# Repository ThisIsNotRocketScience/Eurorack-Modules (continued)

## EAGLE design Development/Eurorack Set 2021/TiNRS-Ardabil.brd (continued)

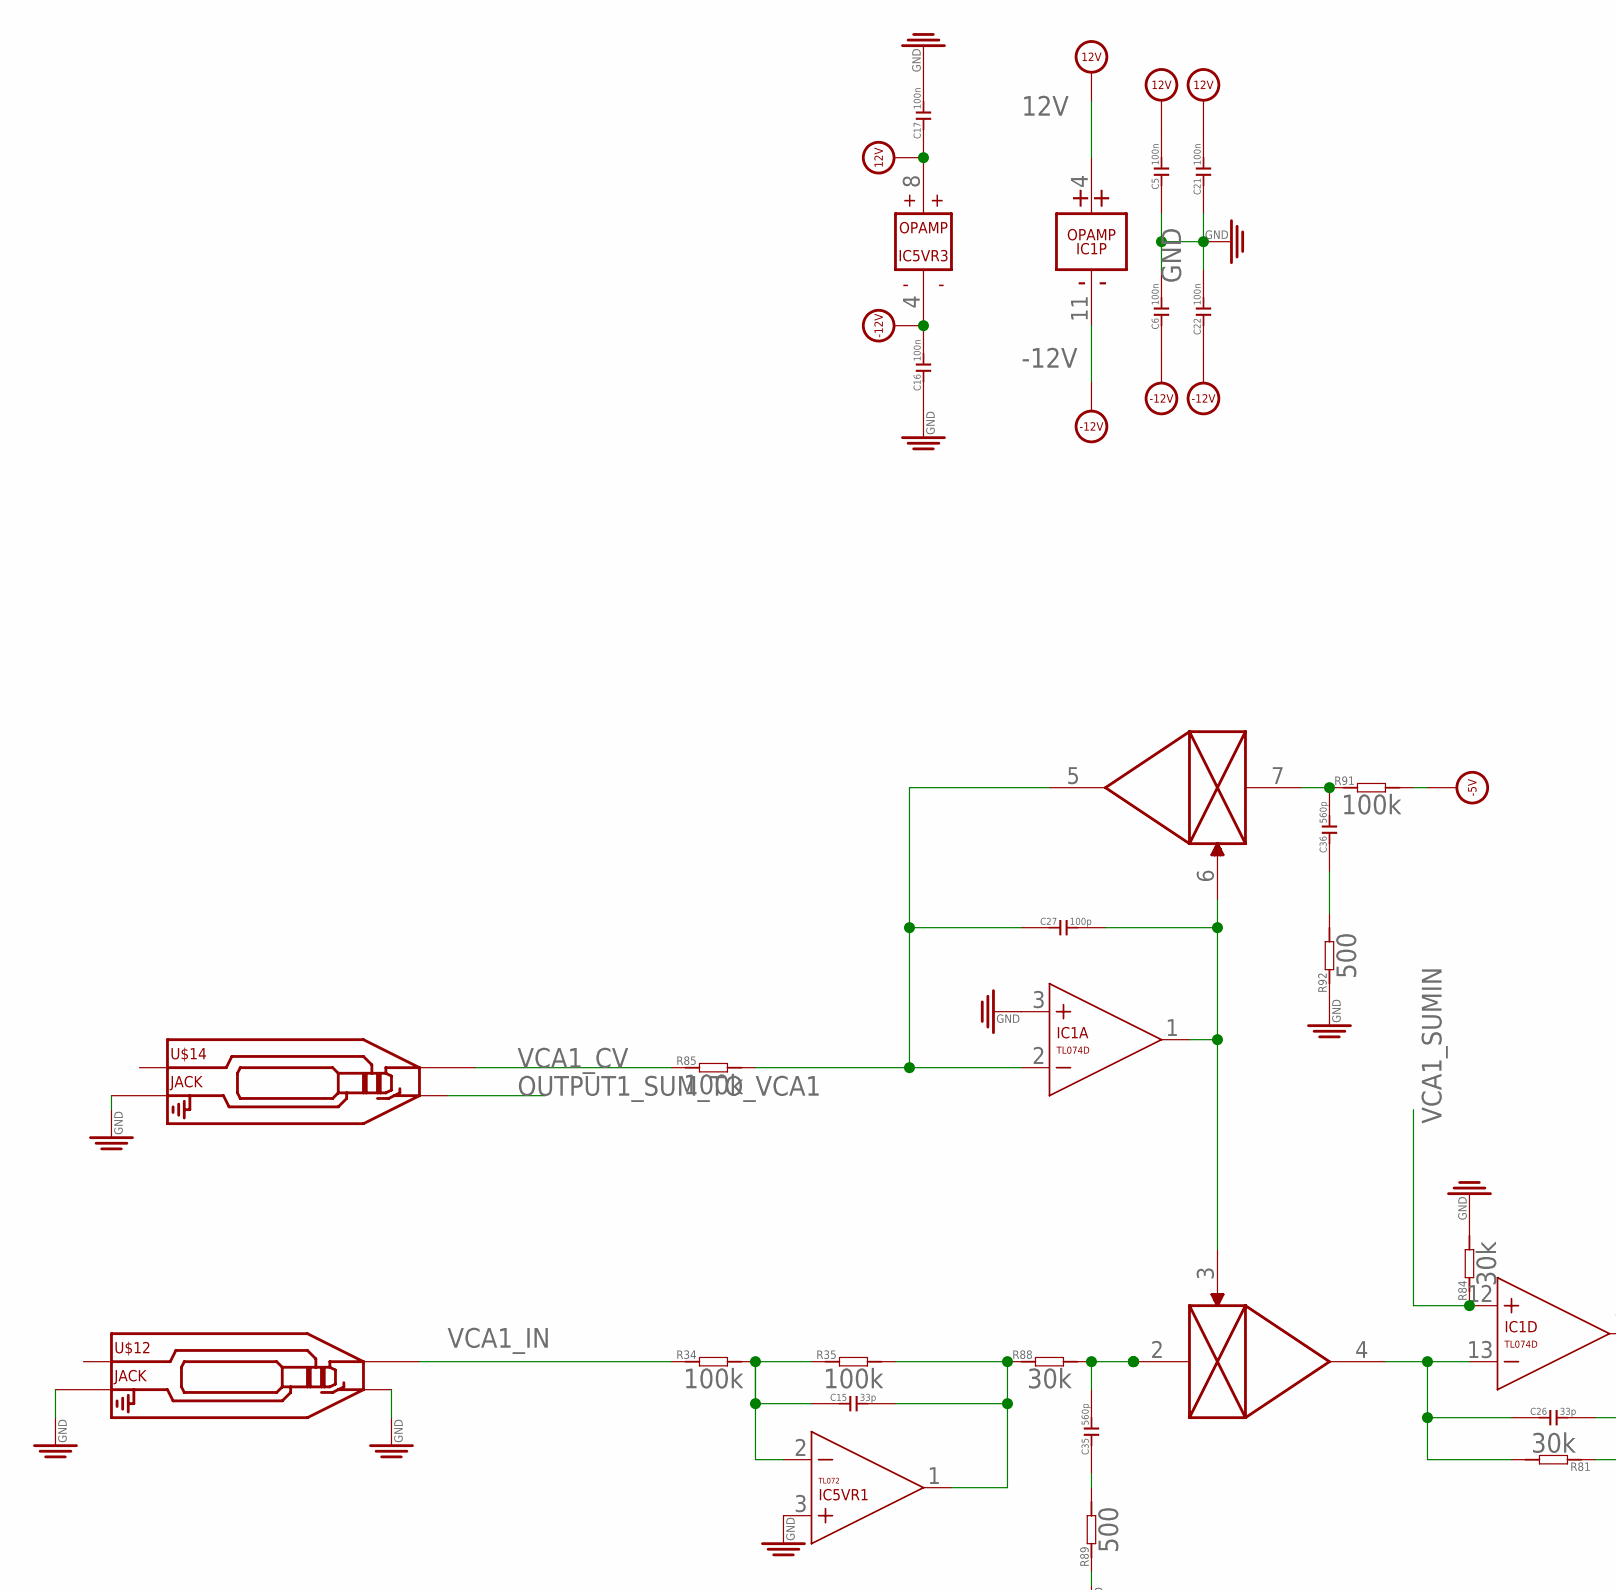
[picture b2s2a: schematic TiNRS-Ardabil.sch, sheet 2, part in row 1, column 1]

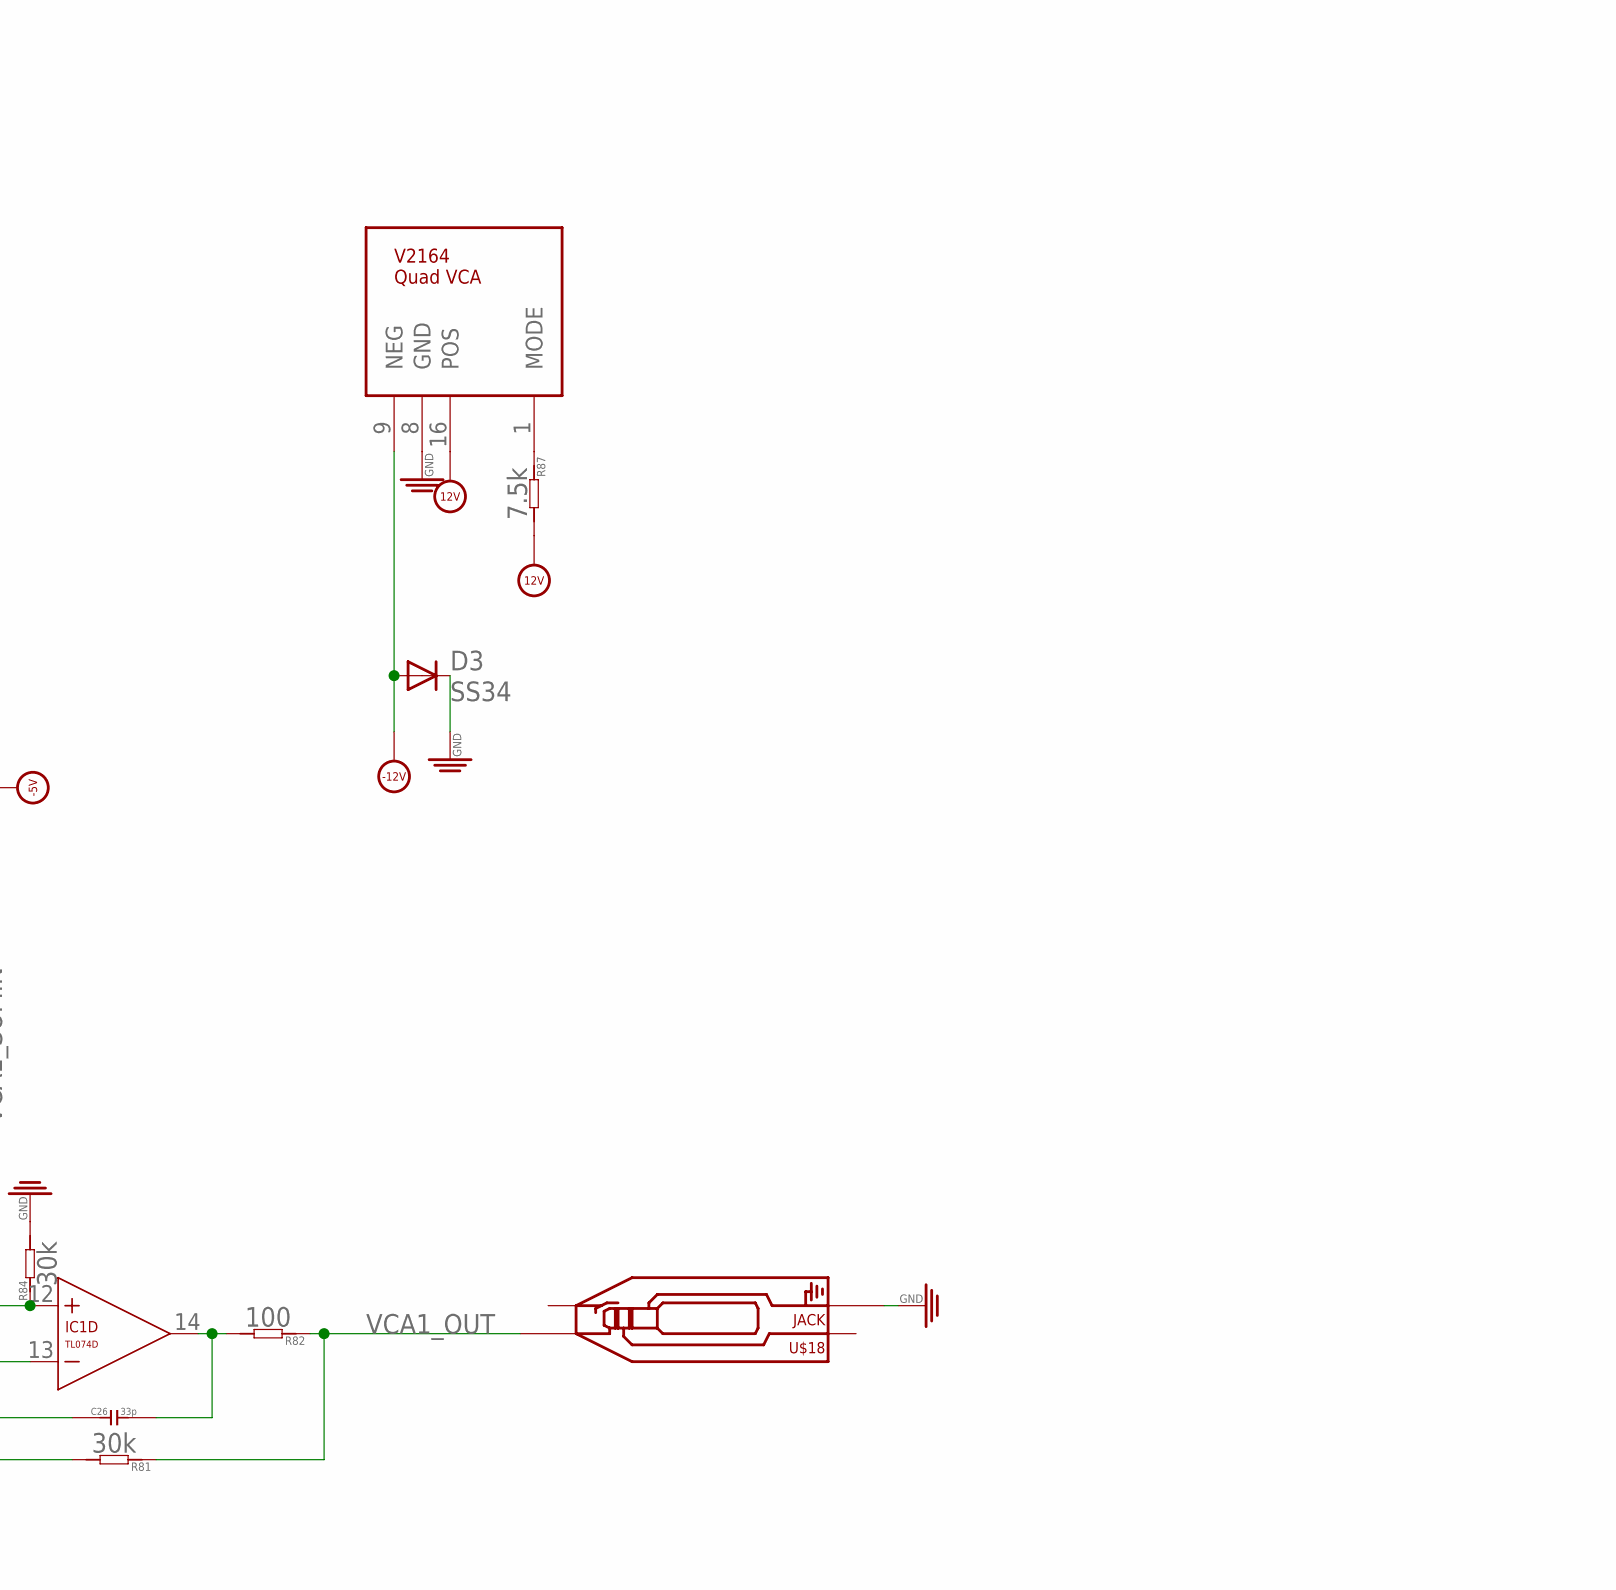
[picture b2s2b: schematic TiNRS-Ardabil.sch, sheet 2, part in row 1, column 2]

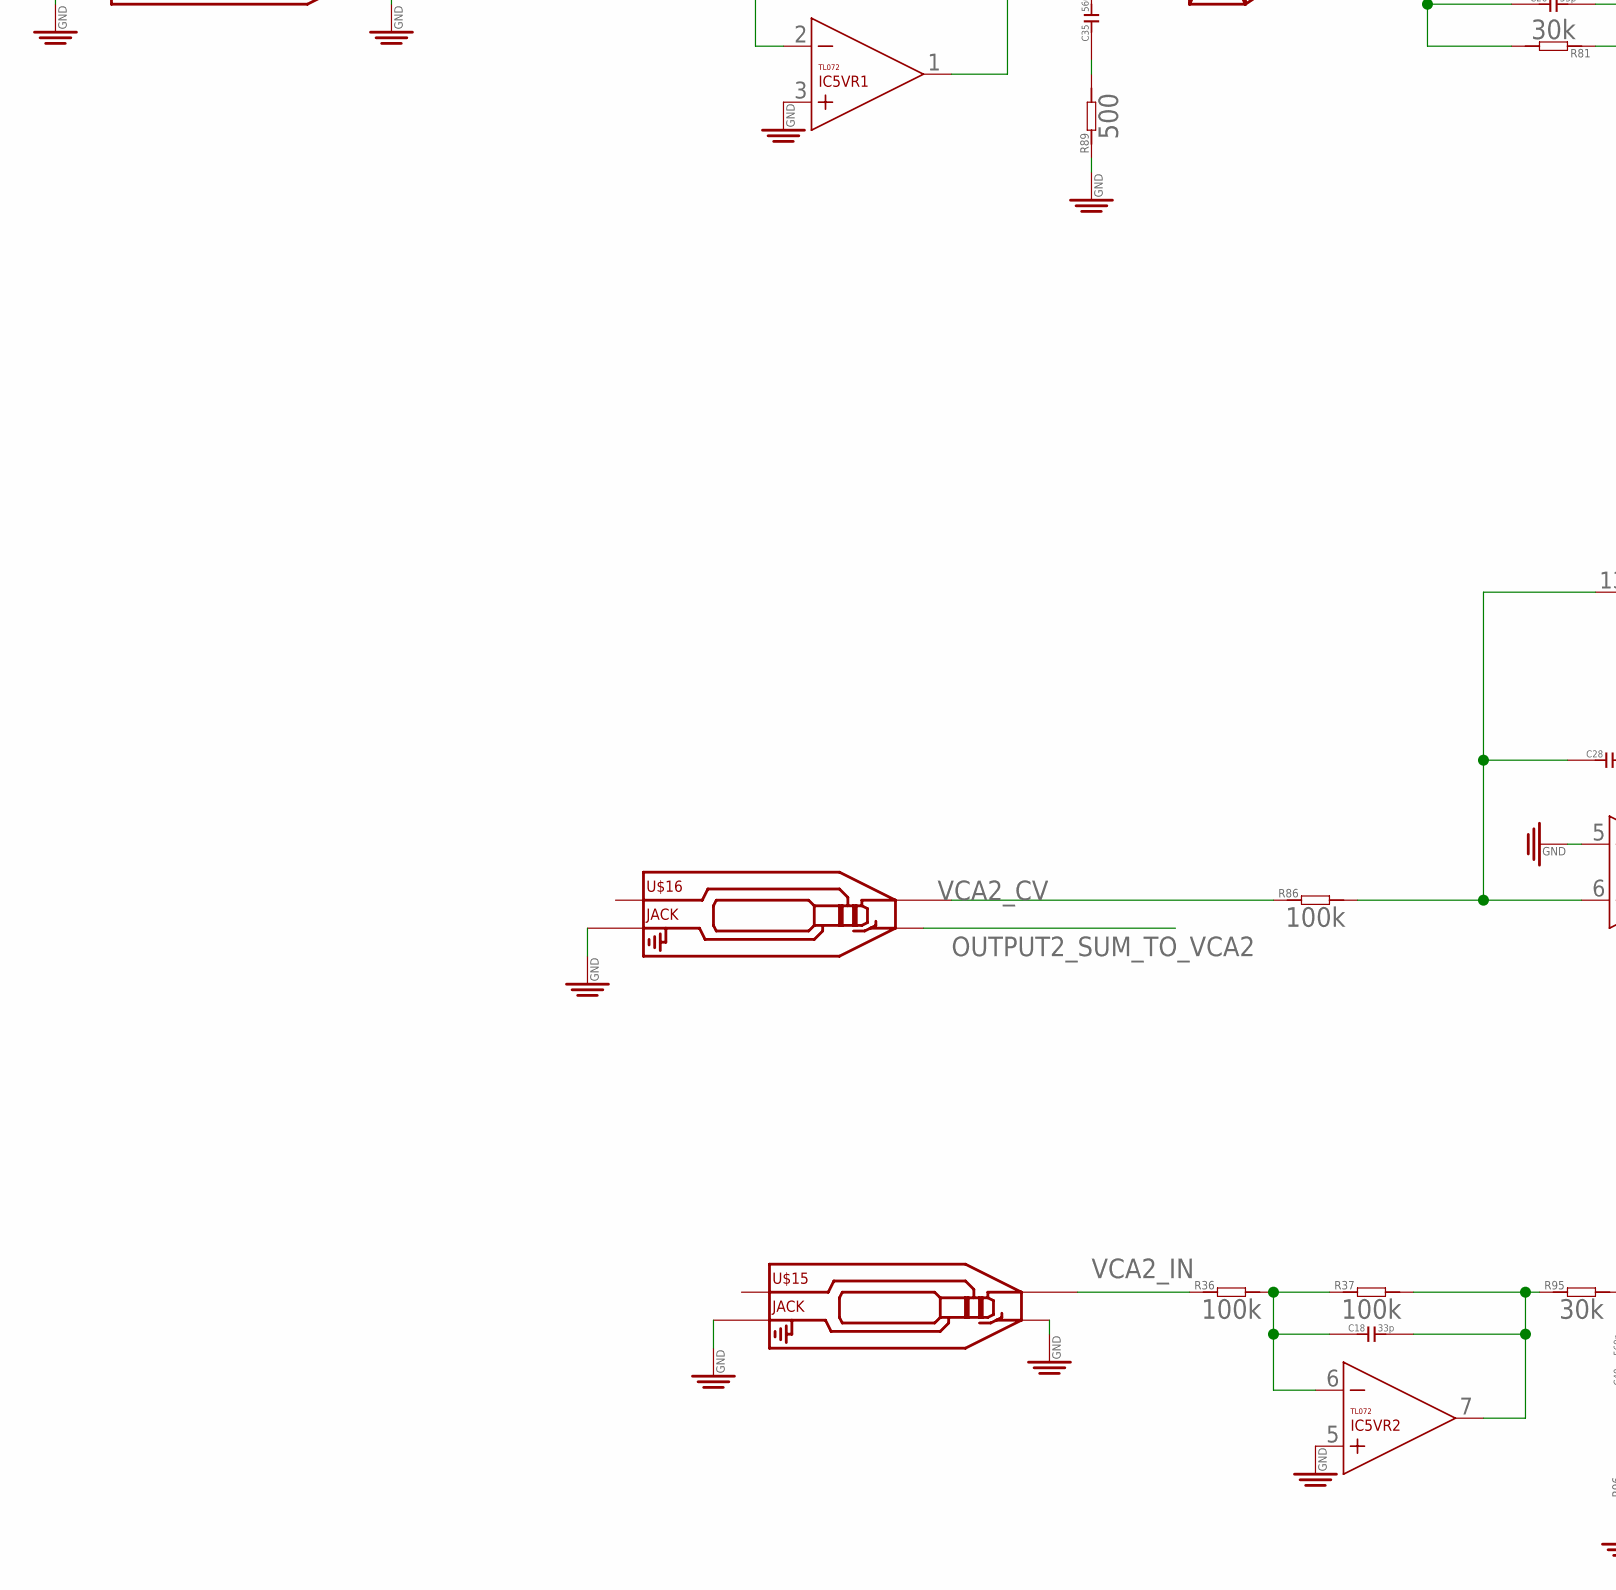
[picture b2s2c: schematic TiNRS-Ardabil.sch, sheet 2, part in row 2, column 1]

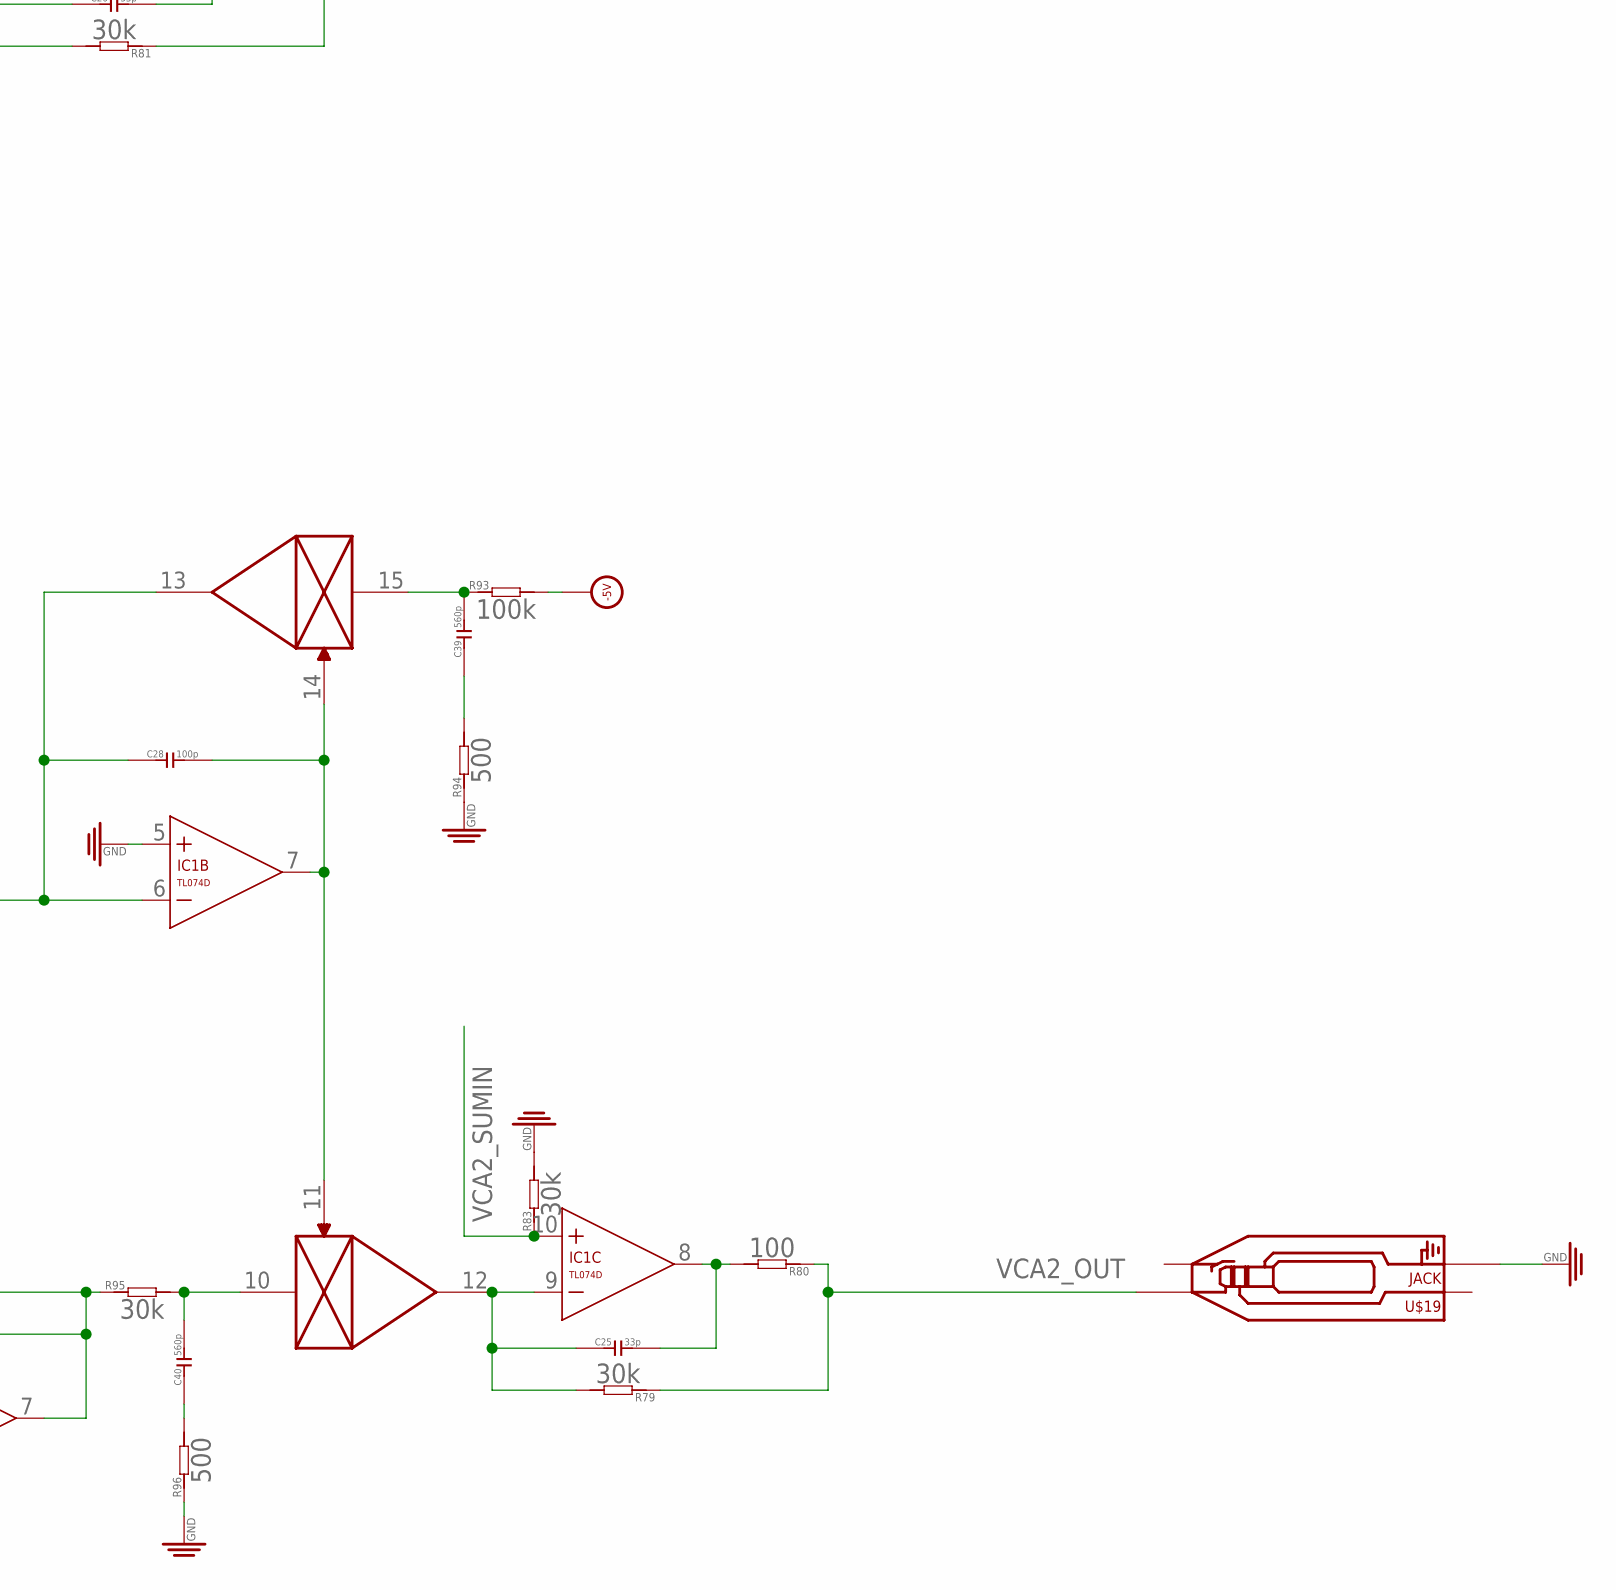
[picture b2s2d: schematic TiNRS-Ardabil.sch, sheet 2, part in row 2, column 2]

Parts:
C5, C6, C16, C17, C21, C22: 100n; C0603
C15, C18, C25, C26: 33p; C0603
C27, C28: 100p; C0603
C35, C36, C39, C40: 560p; C0603
D3: SS34; DO-214AC
IC1: TL074D; SO14
IC5: TL072; SO08
R34, R35, R36, R37, R85, R86, R91, R93: 100k; R0603
R79, R81, R83, R84, R88, R95: 30k; R0603
R80, R82: 100; R0603
R87: 7.5k; R0603
R89, R92, R94, R96: 500; R0603
U$12, U$14, U$15, U$16, U$18, U$19: JACK; 3.5MM-JACK-SWITCH-13MM-NOHOLES-TESTPAD
U$32: V2164; SO16

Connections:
12V: C5.2, C17.1, C21.2, IC1.4 (V+), IC5.8 (V+), R87.2, U$32.16 (POS); also elsewhere on the board
-5V: R91.2, R93.2; also elsewhere on the board
-12V: C6.1, C16.2, C22.1, D3.2 (A), IC1.11 (V-), IC5.4 (V-), U$32.9 (NEG); also elsewhere on the board
GND: C5.1, C6.2, C16.1, C17.2, C21.1, C22.2, D3.1 (C), IC1.3 (+IN), IC1.5 (+IN), IC5.3 (+IN), IC5.5 (+IN), R83.2, R84.2, R89.1, R92.1, R94.1, R96.1, U$12.RING_B@1 (RING), U$12.RING_T@3 (RING), U$12.SWITCH_B@1 (SWITCH), U$12.SWITCH_T@3 (SWITCH), U$14.RING_B@1 (RING), U$14.RING_T@3 (RING), U$15.RING_B@1 (RING), U$15.RING_T@3 (RING), U$15.SWITCH_B@1 (SWITCH), U$15.SWITCH_T@3 (SWITCH), U$16.RING_B@1 (RING), U$16.RING_T@3 (RING), U$18.RING_B@1 (RING), U$18.RING_T@3 (RING), U$19.RING_B@1 (RING), U$19.RING_T@3 (RING), U$32.8 (GND); also elsewhere on the board
unnamed: C15.1, IC5.2 (-IN), R34.2, R35.1
unnamed: C15.2, IC5.1 (OUT), R35.2, R88.1
unnamed: C18.1, IC5.6 (-IN), R36.2, R37.1
unnamed: C18.2, IC5.7 (OUT), R37.2, R95.1
unnamed: C25.2, IC1.8 (OUT), R80.2
unnamed: C25.1, IC1.9 (-IN), R79.2, U$32.12 (OUT)
unnamed: C26.2, IC1.14 (OUT), R82.2
unnamed: C26.1, IC1.13 (-IN), R81.2, U$32.4 (OUT)
unnamed: C27.2, IC1.1 (OUT), U$32.3 (CV), U$32.6 (CV)
unnamed: C28.1, IC1.6 (-IN), R86.2, U$32.13 (OUT)
unnamed: C28.2, IC1.7 (OUT), U$32.11 (CV), U$32.14 (CV)
unnamed: R87.1, U$32.1 (MODE)
unnamed: C35.1, R89.2
unnamed: C35.2, R88.2, U$32.2 (IN)
unnamed: C36.2, R91.1, U$32.7 (IN)
unnamed: C36.1, R92.2
unnamed: C39.2, R93.1, U$32.15 (IN)
unnamed: C39.1, R94.2
unnamed: C40.1, R96.2
unnamed: C40.2, R95.2, U$32.10 (IN)
OUTPUT1_SUM_TO_VCA1: U$14.SWITCH_B@1 (SWITCH), U$14.SWITCH_T@3 (SWITCH); also elsewhere on the board
OUTPUT2_SUM_TO_VCA2: U$16.SWITCH_B@1 (SWITCH), U$16.SWITCH_T@3 (SWITCH); also elsewhere on the board
VCA1_CV: R85.1, U$14.TIP_B@1 (TIP), U$14.TIP_T@3 (TIP)
VCA1_FB: C27.1, IC1.2 (-IN), R85.2, U$32.5 (OUT)
VCA1_IN: R34.1, U$12.TIP_B@1 (TIP), U$12.TIP_T@3 (TIP)
VCA1_OUT: R81.1, R82.1, U$18.TIP_B@1 (TIP), U$18.TIP_T@3 (TIP)
VCA1_SUMIN: IC1.12 (+IN), R84.1
VCA2_CV: R86.1, U$16.TIP_B@1 (TIP), U$16.TIP_T@3 (TIP)
VCA2_IN: R36.1, U$15.TIP_B@1 (TIP), U$15.TIP_T@3 (TIP)
VCA2_OUT: R79.1, R80.1, U$19.TIP_B@1 (TIP), U$19.TIP_T@3 (TIP)
VCA2_SUMIN: IC1.10 (+IN), R83.1

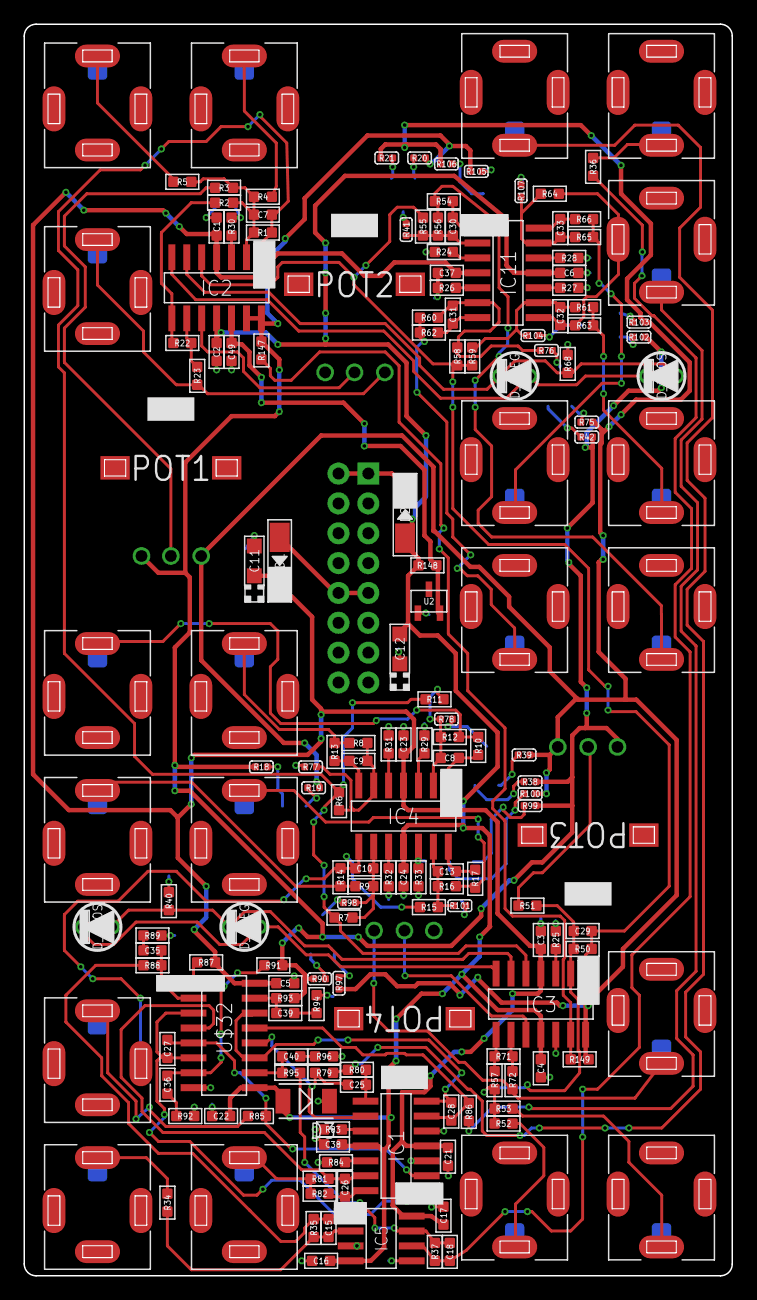
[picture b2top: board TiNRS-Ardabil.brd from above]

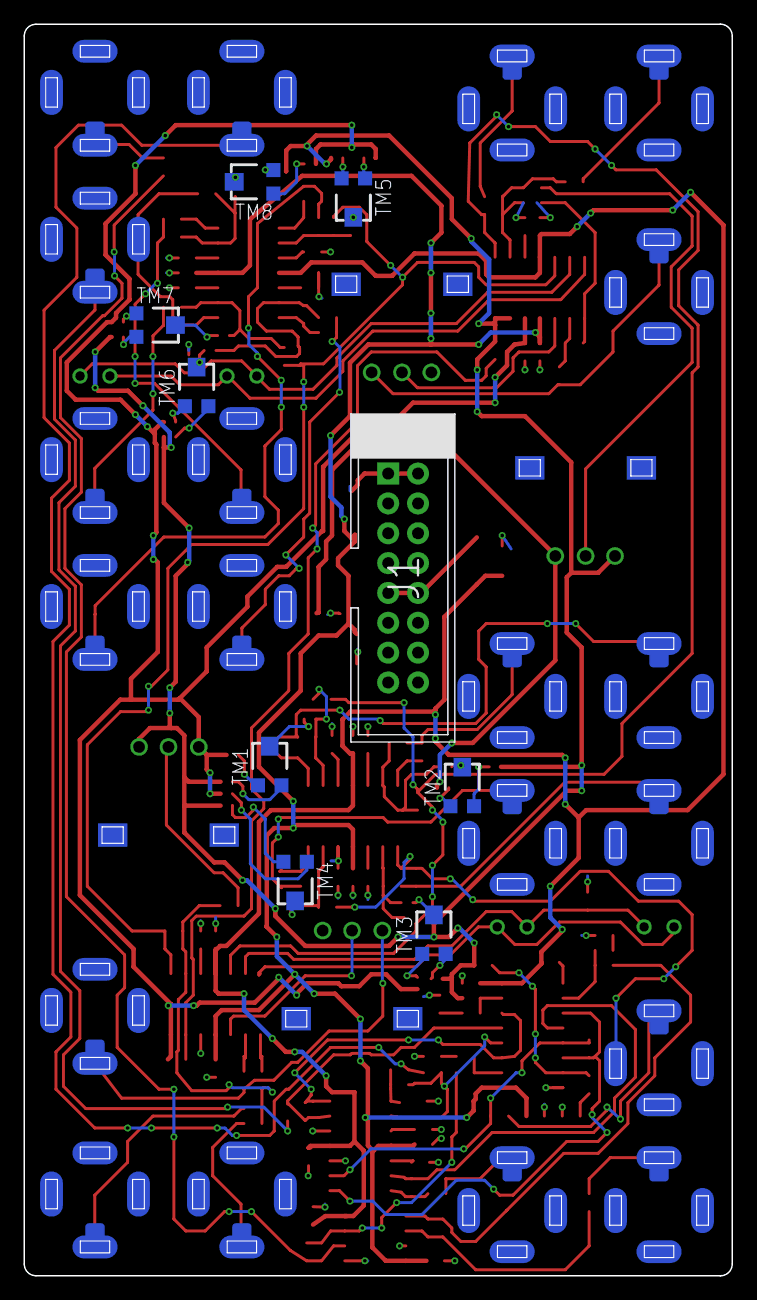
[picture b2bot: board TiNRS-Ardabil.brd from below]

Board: 2 copper layers, 60.2 x 106.5 mm, 184 parts (9 on the bottom side), 118 nets.

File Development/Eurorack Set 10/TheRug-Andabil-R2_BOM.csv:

Comment,Designator,Footprint,LCSC Part #
EURORACK_PCB12HP,"U$1",EURORACK12HPPCB,
MRA4004T3G,"D1, D2",DO-214AC,
10uF,"C11, C12",CASE-A_3216,
PJ-341,"U$2, U$4, U$13, U$3, U$5, U$6, U$17, U$12, U$14, U$15, U$16, U$18, U$19, U$9, U$20, U$25, U$26, U$27, U$28, U$30",3.5MM-JACK-SWITCH-13MM-NOHOLES,
100K 0.1%,"R1, R4, R5, R11, R12, R6, R7, R8, R9, R15, R16, R50, R52, R53, R55, R56, R58, R59, R60, R61, R64, R65",R0603,
100K,"R3, R22, R23, R51, R71, R72, R149, R147",R0603,
56,"R10, R13, R14, R17, R54, R62, R63, R66",R0603,
49.9K,"R2, R57",R0603,
1.2K,"R68, R40",R0603,
10k,"R148",R0603,
30k,"R79, R81, R83, R84, R88, R95",R0603,
100,"R80, R82",R0603,
100k,"R85, R86, R91, R93, R34, R35, R37, R36",R0603,
7.5k,"R87",R0603,
500,"R89, R92, R94, R96",R0603,
51k,"R24, R25, R26, R27, R28, R29, R30, R31, R32, R33",R0603,
10KB,"U$8, U$7, U$29, U$31",ALPS_POT_SQUAREHOLES,
3mm YELLOW,"D_1NEG, D_1POS, D_2NEG, D_2POS",3MMLED,
22pf,"C7, C8, C9, C10, C13, C29, C30, C31, C32, C33",C0603,
100nF,"C49, C23, C24, C37, C38, C1, C2, C3, C4",C0603,
100n,"C5, C6, C21, C22, C16, C17",C0603,
33p,"C25, C26, C15, C18",C0603,
100p,"C27, C28",C0603,
560p,"C35, C36, C39, C40",C0603,
POWERSHROUDED,"J1",POWER_16_SHROUDED,
LM4040DIM3-5.0,"U2",SOT95P237X112-3N,
TL074TSSOP14,"IC4, IC11, IC2, IC3, IC1",TSSOP14,
V2164,"U$32",SO16,
TL072TSSOP8,"IC5",TSSOP8,
